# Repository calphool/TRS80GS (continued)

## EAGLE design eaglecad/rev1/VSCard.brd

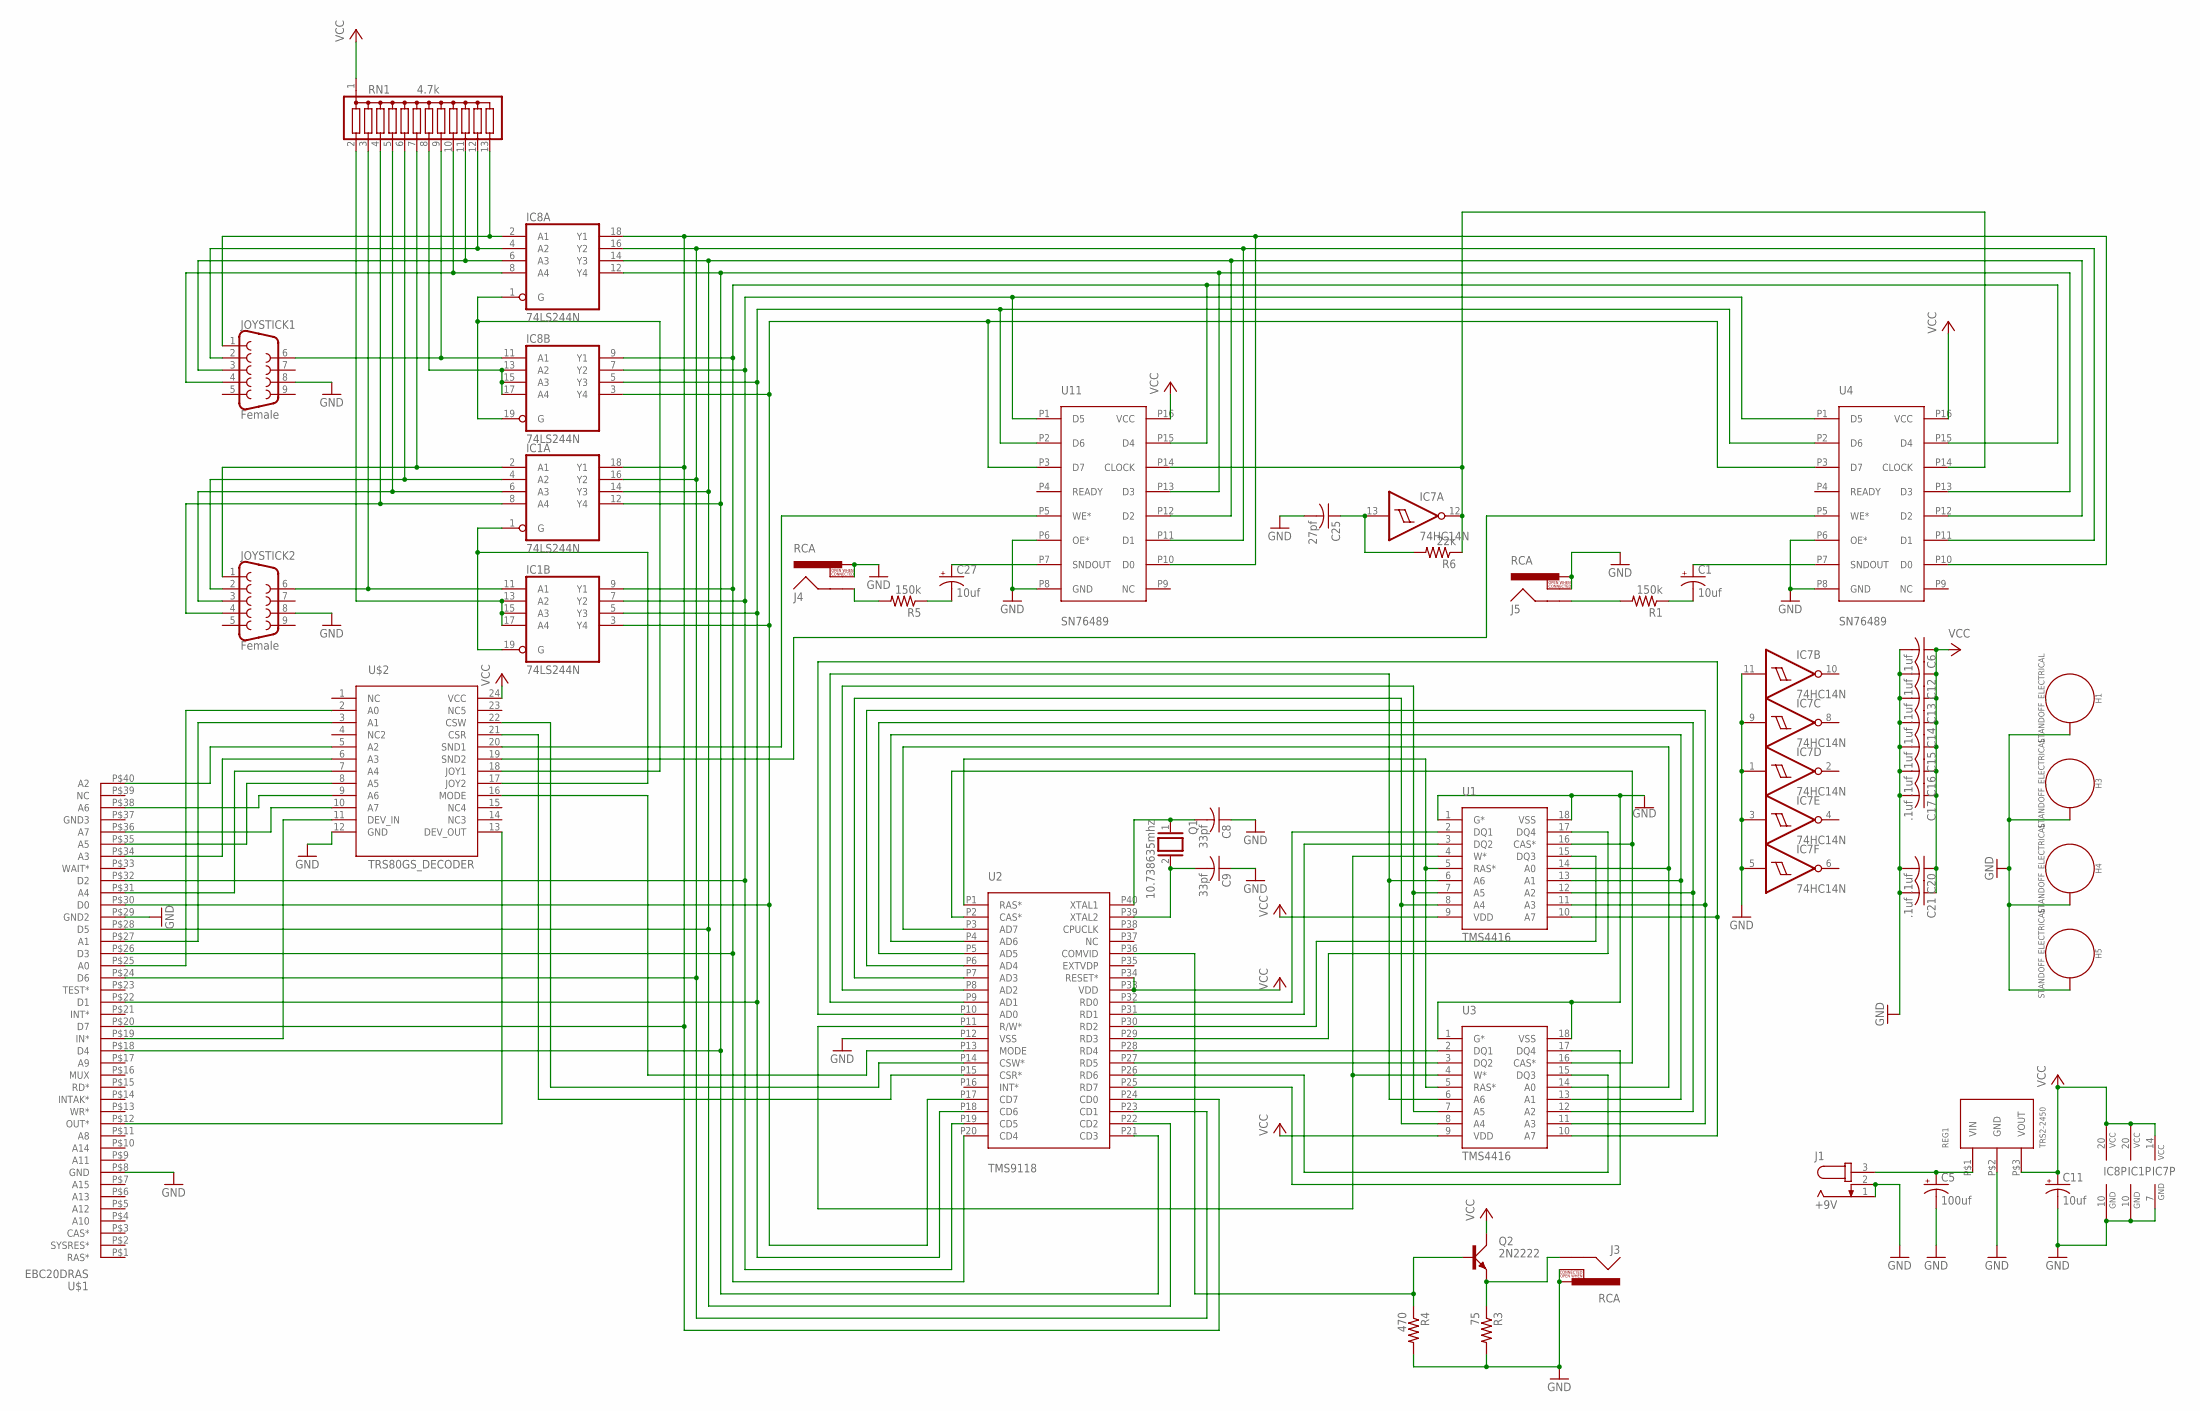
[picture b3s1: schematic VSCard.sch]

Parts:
C1, C27: 10uf; E2,5-6
C5: 100uf; E3,5-10
C6, C12, C13, C14, C15, C16, C17, C20, C21: .1uf; C025-025X050
C8, C9: 33pf; C050-050X075
C11: 10uf; E3,5-10
C25: 27pf; C025-025X050
H1, H3, H4, H5: STANDOFF_ELECTRICAL; STANDOFF-ELECTRICAL
IC1, IC8: 74LS244N; DIL20
IC7: 74HC14N; DIL14
J1: +9V; SPC4077
J3, J4, J5: RCA
JOYSTICK1, JOYSTICK2: Female; DB9
Q1: 10.738635mhz; QS
Q2: 2N2222; TO18A
R1, R5: 150k; 0207/2V
R3: 75; 0207/2V
R4: 470; 0207/2V
R6: 22k; 0207/2V
REG1: TRS2-2450; TRACON_REG
RN1: 4.7k; SIL13
U1, U3: TMS4416; DIP18
U2: TMS9118; DIP40_MCU
U4, U11: SN76489; DIP16
U$1: EBC20DRAS
U$2: TRS80GS_DECODER; DIP24SKI

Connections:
COMVID: Q2.B, R4.1, U2.P36 (COMVID)
COMVID-OUT: J3.SHELL, Q2.E, R3.1
D0: IC1.3 (Y4), IC8.3 (Y4), U2.P17 (CD7), U4.P3 (D7), U11.P3 (D7), U$1.P$30 (D0)
D1: IC1.5 (Y3), IC8.5 (Y3), U2.P18 (CD6), U4.P2 (D6), U11.P2 (D6), U$1.P$22 (D1)
D2: IC1.7 (Y2), IC8.7 (Y2), U2.P19 (CD5), U4.P1 (D5), U11.P1 (D5), U$1.P$32 (D2)
D3: IC1.9 (Y1), IC8.9 (Y1), U2.P20 (CD4), U4.P15 (D4), U11.P15 (D4), U$1.P$26 (D3)
D4: IC1.12 (Y4), IC8.12 (Y4), U2.P21 (CD3), U4.P13 (D3), U11.P13 (D3), U$1.P$18 (D4)
D5: IC1.14 (Y3), IC8.14 (Y3), U2.P22 (CD2), U4.P12 (D2), U11.P12 (D2), U$1.P$28 (D5)
D6: IC1.16 (Y2), IC8.16 (Y2), U2.P23 (CD1), U4.P11 (D1), U11.P11 (D1), U$1.P$24 (D6)
D7: IC1.18 (Y1), IC8.18 (Y1), U2.P24 (CD0), U4.P10 (D0), U11.P10 (D0), U$1.P$20 (D7)
DOWN: IC8.4 (A2), JOYSTICK1.2, RN1.12
DOWN1: IC1.4 (A2), JOYSTICK2.2, RN1.6
GND: C5.-, C6.2, C8.1, C9.1, C11.-, C12.2, C13.2, C14.2, C15.2, C16.2, C17.2, C20.2, C21.2, C25.2, H1.P1, H3.P1, H4.P1, H5.P1, IC1.10 (GND), IC7.1 (I), IC7.3 (I), IC7.5 (I), IC7.7 (GND), IC7.9 (I), IC7.11 (I), IC8.10 (GND), J1.1, J1.2, J3.PIN, J3.SWITCH, J4.PIN, J4.SWITCH, J5.PIN, J5.SWITCH, JOYSTICK1.8, JOYSTICK2.8, R3.2, R4.2, REG1.P$2 (GND), U1.1 (G*), U1.18 (VSS), U2.P12 (VSS), U3.1 (G*), U3.18 (VSS), U4.P6 (OE*), U4.P8 (GND), U11.P6 (OE*), U11.P8 (GND), U$1.P$8 (GND), U$1.P$29 (GND2), U$2.12 (GND)
JOY1_IN_ENABLE_N: IC8.1 (G), IC8.19 (G), U$2.18 (JOY1)
JOY1_IN_ENABLE_N1: IC1.1 (G), IC1.19 (G), U$2.17 (JOY2)
LEFT: IC8.6 (A3), JOYSTICK1.3, RN1.11
LEFT1: IC1.6 (A3), JOYSTICK2.3, RN1.5
unnamed: J4.SHELL, R5.2
unnamed: U$1.P$25 (A0), U$2.2 (A0)
unnamed: U$1.P$27 (A1), U$2.3 (A1)
unnamed: U$1.P$40 (A2), U$2.5 (A2)
unnamed: U$1.P$34 (A3), U$2.6 (A3)
unnamed: U$1.P$31 (A4), U$2.7 (A4)
unnamed: U$1.P$35 (A5), U$2.8 (A5)
unnamed: U$1.P$38 (A6), U$2.9 (A6)
unnamed: U$1.P$36 (A7), U$2.10 (A7)
unnamed: U$1.P$19 (IN*), U$2.11 (DEV_IN)
unnamed: IC1.13 (A2), IC1.15 (A3), IC1.17 (A4), RN1.2
unnamed: U$1.P$12 (OUT*), U$2.13 (DEV_OUT)
unnamed: U2.P13 (MODE), U$2.16 (MODE)
unnamed: U2.P14 (CSW*), U$2.22 (CSW)
unnamed: U2.P15 (CSR*), U$2.21 (CSR)
unnamed: U1.5 (RAS*), U2.P1 (RAS*), U3.5 (RAS*)
unnamed: U11.P5 (WE*), U$2.20 (SND1)
unnamed: U1.16 (CAS*), U2.P2 (CAS*), U3.16 (CAS*)
unnamed: U4.P5 (WE*), U$2.19 (SND2)
unnamed: C27.-, R5.1
unnamed: C25.1, IC7.13 (I), R6.2
unnamed: C1.-, R1.1
unnamed: J5.SHELL, R1.2
unnamed: IC8.13 (A2), IC8.15 (A3), IC8.17 (A4), RN1.8
RIGHT: IC8.8 (A4), JOYSTICK1.4, RN1.10
RIGHT1: IC1.8 (A4), JOYSTICK2.4, RN1.4
SN76489-CLOCK: IC7.12 (O), R6.1, U4.P14 (CLOCK), U11.P14 (CLOCK)
SNDOUT1: C27.+, U11.P7 (SNDOUT)
SNDOUT2: C1.+, U4.P7 (SNDOUT)
TMS9118_RW(*)_TMS4416_W(*): U1.4 (W*), U2.P11 (R/W*), U3.4 (W*)
TMS9918_AD0-TMS4416_A7: U1.10 (A7), U2.P10 (AD0), U3.10 (A7)
TMS9918_AD1-TMS4416_A6: U1.6 (A6), U2.P9 (AD1), U3.6 (A6)
TMS9918_AD2-TMS4416_A5: U1.7 (A5), U2.P8 (AD2), U3.7 (A5)
TMS9918_AD3-TMS4416_A4: U1.8 (A4), U2.P7 (AD3), U3.8 (A4)
TMS9918_AD4-TMS4416_A3: U1.11 (A3), U2.P6 (AD4), U3.11 (A3)
TMS9918_AD5-TMS4416_A2: U1.12 (A2), U2.P5 (AD5), U3.12 (A2)
TMS9918_AD6-TMS4416_A1: U1.13 (A1), U2.P4 (AD6), U3.13 (A1)
TMS9918_AD7-TMS4416_A0: U1.14 (A0), U2.P3 (AD7), U3.14 (A0)
TRIGGER: IC8.11 (A1), JOYSTICK1.6, RN1.9
TRIGGER1: IC1.11 (A1), JOYSTICK2.6, RN1.3
UP: IC8.2 (A1), JOYSTICK1.1, RN1.13
UP1: IC1.2 (A1), JOYSTICK2.1, RN1.7
VCC: C6.1, C11.+, C12.1, C13.1, C14.1, C15.1, C16.1, C17.1, C20.1, C21.1, IC1.20 (VCC), IC7.14 (VCC), IC8.20 (VCC), Q2.C, REG1.P$3 (VOUT), RN1.1, U1.9 (VDD), U2.P33 (VDD), U2.P34 (RESET*), U3.9 (VDD), U4.P16 (VCC), U11.P16 (VCC), U$2.24 (VCC)
VDP-RD0: U1.2 (DQ1), U2.P32 (RD0)
VDP-RD1: U1.3 (DQ2), U2.P31 (RD1)
VDP-RD2: U1.15 (DQ3), U2.P30 (RD2)
VDP-RD3: U1.17 (DQ4), U2.P29 (RD3)
VDP-RD4: U2.P28 (RD4), U3.2 (DQ1)
VDP-RD5: U2.P27 (RD5), U3.3 (DQ2)
VDP-RD6: U2.P26 (RD6), U3.15 (DQ3)
VDP-RD7: U2.P25 (RD7), U3.17 (DQ4)
VOLTAGE-IN: C5.+, J1.3, REG1.P$1 (VIN)
XTAL1: C8.2, Q1.1, U2.P40 (XTAL1)
XTAL2: C9.2, Q1.2, U2.P39 (XTAL2)

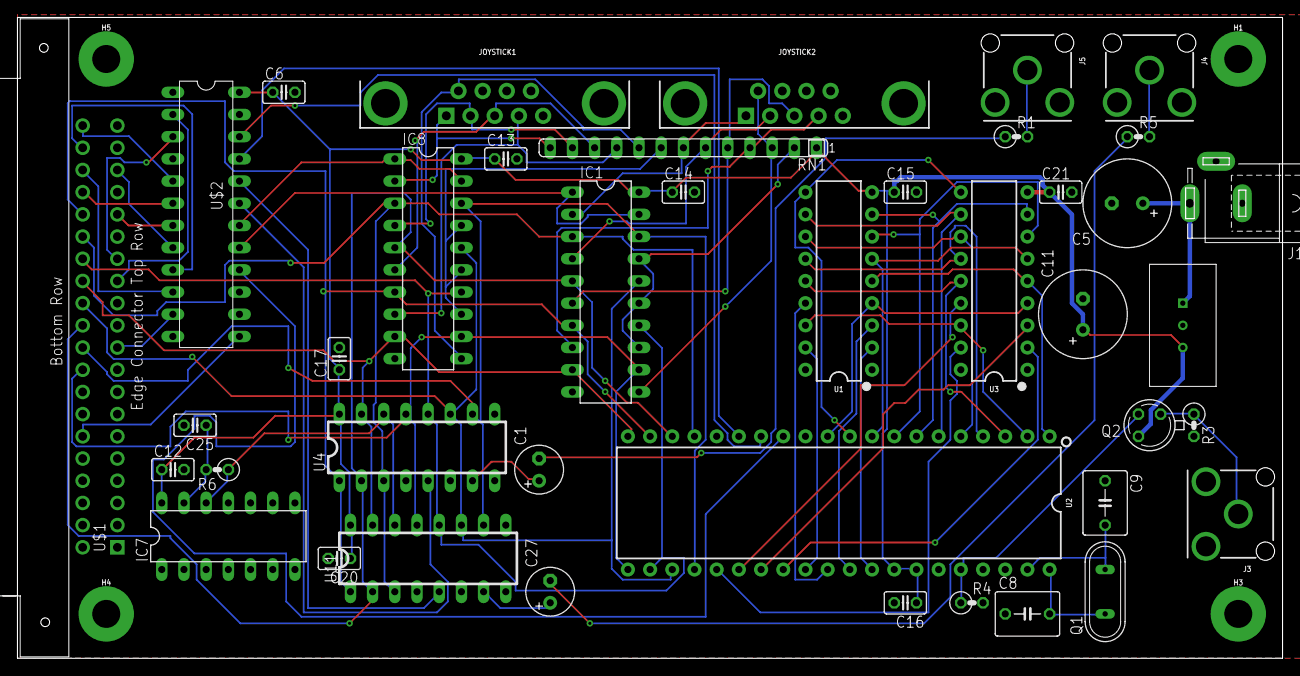
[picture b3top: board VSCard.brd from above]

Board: 2 copper layers, 144.8 x 73.3 mm, 45 parts (0 on the bottom side), 71 nets.

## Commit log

2018-03-11 added TRS-80 snow code / includes cassette .wav file
2018-03-11 TRS80 source code and toolchain
2018-03-11 changed README.md
2018-03-12 minor fix to reset code
2018-03-12 code cleanup in arduino test stuff
2018-03-25 new version with PLD glue logic chip
2018-06-01 v2 graphics/sound design and memboard initial design
2018-06-01 added TRS-80 Model 1 Level 2 Basic test program for v2 of graphics/sound card
2018-06-01 added picture of prototype card
2018-06-01 added photo
2018-06-01 readme.md fix
2018-06-01 seriously? 'stuch' instead of such?
2018-06-01 more updates to README.md
2018-06-03 added z88dk test program
2018-06-05 pacman clone initial upload
2018-06-06 changes to pacman game
2018-06-07 pacman update
2018-06-15 schematic updates
2018-06-15 add pdfs
2018-06-16 board with SRAM
2018-06-24 added note data code
2018-06-28 added revised card that includes improved clock circuit
2018-07-09 updated pacman code
2018-07-14 New PLD Code & new pacman
2018-07-14 version 4 of the board -- adds UART
2018-07-15 added version 3 photo
2018-07-15 new photo
2018-07-24 got rid of extra crystal for UART -- used VDP CPUCLK output instead
2018-07-25 initial UART tests
2018-07-25 updates for rev4
2018-07-26 updated uart code
2018-07-27 minor uart fixes
2018-07-27 README updates
2018-07-29 updated uart code -- first working version
2018-07-30 more uart coding
2018-07-31 uart code fixes
2018-08-19 updated uart handler code
2018-11-04 uart stuff - cmd files that can be uploaded
